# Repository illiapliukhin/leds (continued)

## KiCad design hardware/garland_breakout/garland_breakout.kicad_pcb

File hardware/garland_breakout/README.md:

# Garland breakout v1

A passive fan-out between the mono electronics board's FFC pair and long wire runs (LED nets/garlands, remote panels). It follows [LED_INTERFACE_STANDARD.md](../common/LED_INTERFACE_STANDARD.md). To the cable it looks exactly like a panel: same FH12 footprint, cloned from `mono_panel_32x32` `J_ROW`, on B.Cu, cable exits west, pin 1 north, standard **Type B pin 1→1** FFC.

| | |
|---|---|
| Size | 60 × 145 mm, 2 layers, 1.6 mm, 1 oz, 4 × M3 plated (GND) |
| Inputs | `J_ROW`, `J_COL`: FH12-40S-0.5SH, both on the west edge (row cable above the column cable, so the two cables from `J_ROW1`/`J_COL1` run straight) |
| Outputs | `J_R1` rows 1–16, `J_R2` rows 17–32, `J_C1` cols 1–16, `J_C2` cols 17–32: 2×8 2.54 mm IDC box headers; **header pin n = line n = ribbon conductor n** |
| ESD | 64 × PESD5V0S1BL (bidirectional 5 V, SOD-882) from every line to GND, placed at the bus vias next to the headers |
| Row lines | 0.4 mm on the bus/F.Cu, 0.3 mm between header pins, 0.2 mm only in the 0.5 mm-pitch FFC escape (< 30 mm). Total breakout row resistance < 30 mΩ. |
| ID | `U_ID` 24LC02BT-I/OT at 0x50 on J_ROW 35/36/37, 100 nF, WP = GND; J_ROW 33/38/39/40 = GND (`ID_PRESENT_N` asserted) |
| Sense | `TP_VSENSE`: J_ROW pin 34 brought to a test pad (panel-end VLED/row tap for diagnostics) |
| Injection | `J_INJ` 3.5 mm 2-pole terminal, DNP: pin 1 GND (installation earth / ESD return), pin 2 `VINJ` (reserved for a future active row-repeater. A passive matrix cannot use remote VLED, see the standard §5) |
| J_COL spares | 33/38/40 GND; 34–37, 39 (`EXP_*`) left unconnected (reserved for column expansion) |

Assembly: all SMD on **B.Cu** (one reflow side). Only the IDC headers (and DNP J_INJ) are THT, on F.

Optional row-current sense was considered and left out of v1. Only one row is on at a time, so one shunt in the common `LED_4V1` feed on the main board measures the same thing more accurately than 32 series parts at 1.27 mm pitch. `TP_VSENSE` plus the EEPROM `row_path_mohm` field cover drop diagnostics.

## Files

| File | |
|---|---|
| `gen_garland_breakout.py` | parametric generator (KiCad 10 pcbnew, AppImage python3.11) |
| `make_fab.sh` | regenerate → DRC → renders → gerbers/drill/CPL → `fab/garland_breakout_fab.zip` |
| `garland_breakout.kicad_pcb` / `.kicad_pro` | board |
| `fab/drc_report.txt` | **0 violations, 0 unconnected** (KiCad 10, zones refilled) |
| `fab/garland_breakout_fab.zip` | Gerbers (Cu/mask/paste/silk/edge), Excellon, BOM, CPL |
| `fab/garland_breakout_bom.csv`, `fab/garland_breakout_cpl.csv` | |
| `img/garland_breakout_{top,bottom,iso}.png` | renders (no 3D models in the AppImage, so parts show as pads) |

## Price estimate (JLCPCB/LCSC class, Oct 2026, unverified, ±30 %)

| Item | 5 pcs | 50 pcs |
|---|---:|---:|
| PCB 60×145 2L HASL | ~$10 | ~$35 |
| SMT setup + stencil (one side) | ~$10 | ~$10 |
| Extended-part fees (FH12, PESD, 24LC02) | ~$9 | ~$9 |
| Parts per board: 2× FH12 ($1.8), 64× PESD5V0S1BL ($1.6), 4× IDC 2×8 box ($0.8), 24LC02 + C ($0.25) | ~$22 | ~$200 (~$4.0 ea) |
| Hand-solder 4 IDC headers (THT) | own time | ~$15 |
| **Total** | **≈ $50 (≈ $10/board)** | **≈ $270 (≈ $5.5/board)** |
| + 2 × Type B 40p 0.5 mm FFC 100–150 mm | ~$1/board | |
| + 4 × 16-way IDC sockets + 28 AWG ribbon 3 m | ~$3/board | |

## Bring-up checks

1. Continuity: J_ROW pin n ↔ J_R1/J_R2 pin n, J_COL pin n ↔ J_C1/J_C2 pin n (all 64). TVS to GND reads as a diode both ways (≈ 0.6–7 V on the diode tester; no shorts).
2. Without the main-board ID wiring (see LED_SCALING_OPTIONS.md, main-board changes), firmware falls back to the default profile. The LEDs still work.
3. Program `U_ID` with `firmware/panel_id/mkpanelid.py --preset garland32` (an external SOT-23 clip programmer works before the main board has the ID wiring).

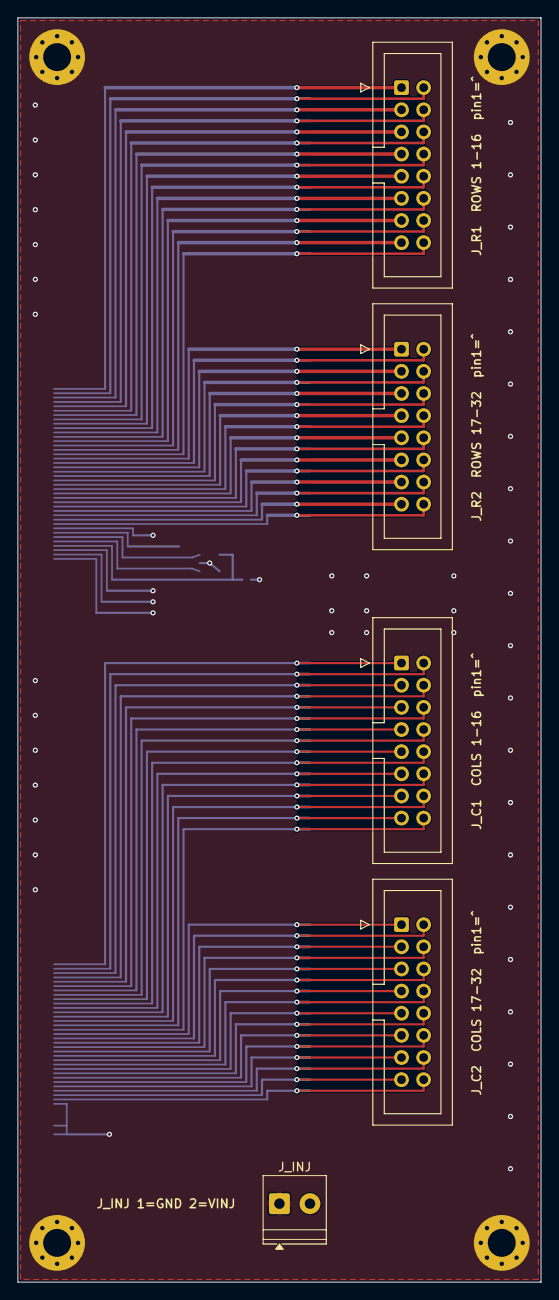
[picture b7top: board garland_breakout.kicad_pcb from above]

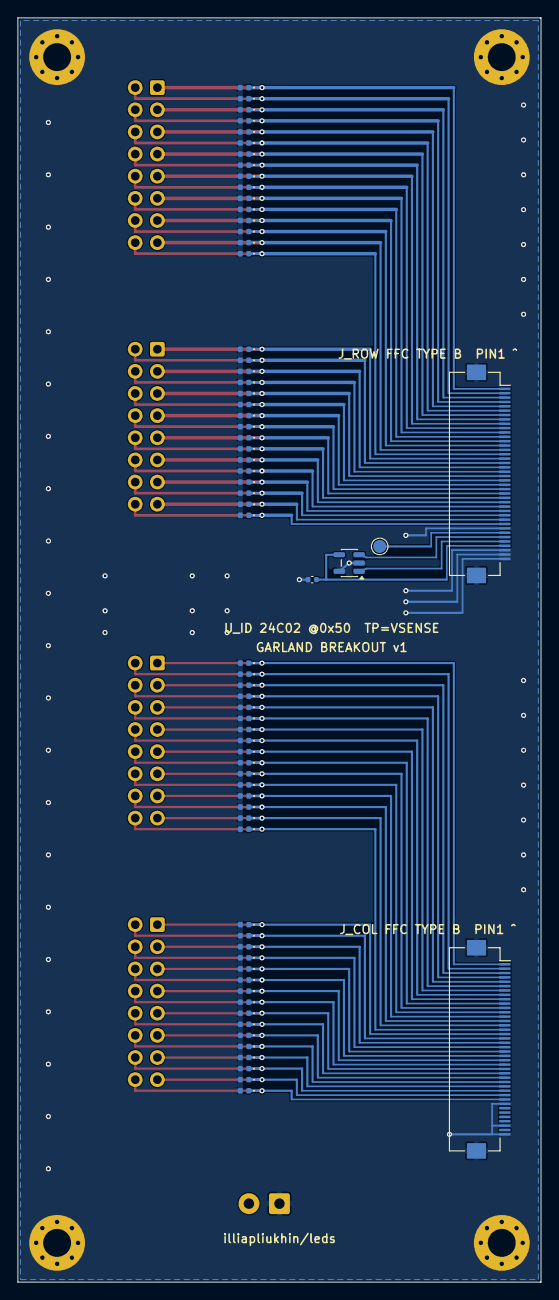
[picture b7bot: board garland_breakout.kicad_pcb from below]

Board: 2 copper layers, 60.0 x 145.0 mm, 78 parts (69 on the bottom side), 69 nets.

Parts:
C_ID: 100n; C_0402_1005Metric
D_C01, D_C02, D_C03, D_C04, D_C05, D_C06, D_C07, D_C08, D_C09, D_C10, D_C11, D_C12, D_C13, D_C14, D_C15, D_C16, D_C17, D_C18, D_C19, D_C20, D_C21, D_C22, D_C23, D_C24, D_C25, D_C26, D_C27, D_C28, D_C29, D_C30, D_C31, D_C32: PESD5V0S1BL; D_0402_1005Metric
D_R01, D_R02, D_R03, D_R04, D_R05, D_R06, D_R07, D_R08, D_R09, D_R10, D_R11, D_R12, D_R13, D_R14, D_R15, D_R16, D_R17, D_R18, D_R19, D_R20, D_R21, D_R22, D_R23, D_R24, D_R25, D_R26, D_R27, D_R28, D_R29, D_R30, D_R31, D_R32: PESD5V0S1BL; D_0402_1005Metric
H1, H2, H3, H4: M3 GND; MountingHole_3.2mm_M3_Pad_Via
J_C1: IDC 2x8 COLS 1-16; IDC-Header_2x08_P2.54mm_Vertical
J_C2: IDC 2x8 COLS 17-32; IDC-Header_2x08_P2.54mm_Vertical
J_COL: FH12-40S-0.5SH; FFC_40P_050_ROW
J_INJ: VINJ/GND (DNP); TerminalBlock_Phoenix_PT-1,5-2-3.5-H_1x02_P3.50mm_Horizontal
J_R1: IDC 2x8 ROWS 1-16; IDC-Header_2x08_P2.54mm_Vertical
J_R2: IDC 2x8 ROWS 17-32; IDC-Header_2x08_P2.54mm_Vertical
J_ROW: FH12-40S-0.5SH; FFC_40P_050_ROW
TP_VSENSE: VLED_SENSE; TestPoint_Pad_D1.5mm
U_ID: 24LC02BT-I/OT; SOT-23-5

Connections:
COL_01: D_C01.1, J_C1.1, J_COL.1
COL_02: D_C02.1, J_C1.2, J_COL.2
COL_03: D_C03.1, J_C1.3, J_COL.3
COL_04: D_C04.1, J_C1.4, J_COL.4
COL_05: D_C05.1, J_C1.5, J_COL.5
COL_06: D_C06.1, J_C1.6, J_COL.6
COL_07: D_C07.1, J_C1.7, J_COL.7
COL_08: D_C08.1, J_C1.8, J_COL.8
COL_09: D_C09.1, J_C1.9, J_COL.9
COL_10: D_C10.1, J_C1.10, J_COL.10
COL_11: D_C11.1, J_C1.11, J_COL.11
COL_12: D_C12.1, J_C1.12, J_COL.12
COL_13: D_C13.1, J_C1.13, J_COL.13
COL_14: D_C14.1, J_C1.14, J_COL.14
COL_15: D_C15.1, J_C1.15, J_COL.15
COL_16: D_C16.1, J_C1.16, J_COL.16
COL_17: D_C17.1, J_C2.1, J_COL.17
COL_18: D_C18.1, J_C2.2, J_COL.18
COL_19: D_C19.1, J_C2.3, J_COL.19
COL_20: D_C20.1, J_C2.4, J_COL.20
COL_21: D_C21.1, J_C2.5, J_COL.21
COL_22: D_C22.1, J_C2.6, J_COL.22
COL_23: D_C23.1, J_C2.7, J_COL.23
COL_24: D_C24.1, J_C2.8, J_COL.24
COL_25: D_C25.1, J_C2.9, J_COL.25
COL_26: D_C26.1, J_C2.10, J_COL.26
COL_27: D_C27.1, J_C2.11, J_COL.27
COL_28: D_C28.1, J_C2.12, J_COL.28
COL_29: D_C29.1, J_C2.13, J_COL.29
COL_30: D_C30.1, J_C2.14, J_COL.30
COL_31: D_C31.1, J_C2.15, J_COL.31
COL_32: D_C32.1, J_C2.16, J_COL.32
GND: C_ID.2, D_C01.2, D_C02.2, D_C03.2, D_C04.2, D_C05.2, D_C06.2, D_C07.2, D_C08.2, D_C09.2, D_C10.2, D_C11.2, D_C12.2, D_C13.2, D_C14.2, D_C15.2, D_C16.2, D_C17.2, D_C18.2, D_C19.2, D_C20.2, D_C21.2, D_C22.2, D_C23.2, D_C24.2, D_C25.2, D_C26.2, D_C27.2, D_C28.2, D_C29.2, D_C30.2, D_C31.2, D_C32.2, D_R01.2, D_R02.2, D_R03.2, D_R04.2, D_R05.2, D_R06.2, D_R07.2, D_R08.2, D_R09.2, D_R10.2, D_R11.2, D_R12.2, D_R13.2, D_R14.2, D_R15.2, D_R16.2, D_R17.2, D_R18.2, D_R19.2, D_R20.2, D_R21.2, D_R22.2, D_R23.2, D_R24.2, D_R25.2, D_R26.2, D_R27.2, D_R28.2, D_R29.2, D_R30.2, D_R31.2, D_R32.2, H1.1, H2.1, H3.1, H4.1, J_COL.33, J_COL.38, J_COL.40, J_COL.MP, J_INJ.1, J_ROW.33, J_ROW.38, J_ROW.39, J_ROW.40, J_ROW.MP, U_ID.2, U_ID.5
ID_3V3: C_ID.1, J_ROW.37, U_ID.4
ID_SCL: J_ROW.36, U_ID.1
ID_SDA: J_ROW.35, U_ID.3
ROW_01: D_R01.1, J_R1.1, J_ROW.1
ROW_02: D_R02.1, J_R1.2, J_ROW.2
ROW_03: D_R03.1, J_R1.3, J_ROW.3
ROW_04: D_R04.1, J_R1.4, J_ROW.4
ROW_05: D_R05.1, J_R1.5, J_ROW.5
ROW_06: D_R06.1, J_R1.6, J_ROW.6
ROW_07: D_R07.1, J_R1.7, J_ROW.7
ROW_08: D_R08.1, J_R1.8, J_ROW.8
ROW_09: D_R09.1, J_R1.9, J_ROW.9
ROW_10: D_R10.1, J_R1.10, J_ROW.10
ROW_11: D_R11.1, J_R1.11, J_ROW.11
ROW_12: D_R12.1, J_R1.12, J_ROW.12
ROW_13: D_R13.1, J_R1.13, J_ROW.13
ROW_14: D_R14.1, J_R1.14, J_ROW.14
ROW_15: D_R15.1, J_R1.15, J_ROW.15
ROW_16: D_R16.1, J_R1.16, J_ROW.16
ROW_17: D_R17.1, J_R2.1, J_ROW.17
ROW_18: D_R18.1, J_R2.2, J_ROW.18
ROW_19: D_R19.1, J_R2.3, J_ROW.19
ROW_20: D_R20.1, J_R2.4, J_ROW.20
ROW_21: D_R21.1, J_R2.5, J_ROW.21
ROW_22: D_R22.1, J_R2.6, J_ROW.22
ROW_23: D_R23.1, J_R2.7, J_ROW.23
ROW_24: D_R24.1, J_R2.8, J_ROW.24
ROW_25: D_R25.1, J_R2.9, J_ROW.25
ROW_26: D_R26.1, J_R2.10, J_ROW.26
ROW_27: D_R27.1, J_R2.11, J_ROW.27
ROW_28: D_R28.1, J_R2.12, J_ROW.28
ROW_29: D_R29.1, J_R2.13, J_ROW.29
ROW_30: D_R30.1, J_R2.14, J_ROW.30
ROW_31: D_R31.1, J_R2.15, J_ROW.31
ROW_32: D_R32.1, J_R2.16, J_ROW.32
VLED_SENSE: J_ROW.34, TP_VSENSE.1

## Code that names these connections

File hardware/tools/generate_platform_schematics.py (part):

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            "FootprintStatus": "RELEASED_MURATA_DFE201612E",
        },
    )
    add_pin_label(schematic, key, "L1", "1", "LED_SW1")
    add_pin_label(schematic, key, "L1", "2", "LED_SW2")
    add_resistor(
        schematic, key, "R3", "655k 0.1%", (185.42, 48.26), "LED_4V1", "LED_FB"
    )
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            "FootprintStatus": "RELEASED_LUCKI_SMD3225_4P",
        },
    )
    add_pin_label(schematic, key, "Y1", "1", "XTAL_P")
    add_pin_label(schematic, key, "Y1", "2", "GND")
    add_pin_label(schematic, key, "Y1", "3", "XTAL_N")
    add_pin_label(schematic, key, "Y1", "4", "GND")
    add_component(
        schematic,
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            "FootprintStatus": "RELEASED_STANDARD_0402",
        },
    )
    add_pin_label(schematic, key, "TH1", "1", "PCB_NTC_ADC")
    add_pin_label(schematic, key, "TH1", "2", "GND")
    add_resistor(
        schematic,
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            "FootprintStatus": "RELEASED_PANASONIC_EVPBL",
        },
    )
    add_pin_label(schematic, key, "SW1", "1", "BUTTON_WAKE_N")
    add_pin_label(schematic, key, "SW1", "2", "GND")
    add_resistor(
        schematic,
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            "FootprintStatus": "RELEASED_GETTOP_V8",
        },
    )
    add_pin_label(schematic, key, "MIC1", "1", "MIC_VDD")
    add_pin_label(schematic, key, "MIC1", "2", "GND")
    add_pin_label(schematic, key, "MIC1", "3", "GND")
    add_pin_label(schematic, key, "MIC1", "4", "MIC_RAW")
    add_component(
        schematic,
        generation_key=key,
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
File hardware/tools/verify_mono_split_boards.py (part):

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    r"\b(?:GND|VBUS|AON_3V3|SYS|REXT1|REXT2|LED_LOGIC_3V3|LED_OE_N|"
    r"LED_CLK(?:_(?:Y|PRE))?|LED_SDI(?:_(?:Y|PRE))?|LED_LE(?:_(?:Y|PRE))?|"
    r"LED_OE_Y|LED_SDO|LED_FB|SW_L1|SW_L2|LED_EN|LED_LOGIC_EN|LED_QOD|"
    r"AUDIO_EN|BAT_RAW|ILIM_VSET|TS_MR|ISET|CHIP_PU|GPIO0_BOOT|"
    r"USB_D_P(?:_MCU)?|USB_D_N(?:_MCU)?|XTAL_P|XTAL_N)\b"
)

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
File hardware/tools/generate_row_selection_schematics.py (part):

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        },
    )

    add_pin_label(schematic, generation_key, reference, "1", "AON_3V3")
    add_pin_label(schematic, generation_key, reference, "2", "AON_3V3")
    for address_index in range(4):
        add_pin_label(
            schematic,
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            str(3 + address_index),
            f"ROW_A{address_index}",
        )
    add_pin_label(schematic, generation_key, reference, "7", "DEC_A_EN_N")
    add_pin_label(schematic, generation_key, reference, "8", "DEC_B_EN_N")
    add_pin_label(
        schematic,
        generation_key,
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
    add_no_connect(schematic, generation_key, reference, "14")
    add_no_connect(schematic, generation_key, reference, "15")
    add_pin_label(schematic, generation_key, reference, "16", "DEC_B_EN_4V1_N")
    add_pin_label(schematic, generation_key, reference, "17", "DEC_A_EN_4V1_N")
    for address_index, pin_number in enumerate(("21", "20", "19", "18")):
        add_pin_label(
            schematic,
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            pin_number,
            f"ROW_A{address_index}_4V1",
        )
    add_pin_label(schematic, generation_key, reference, "22", "ROW_XLAT_OE_N")
    add_pin_label(schematic, generation_key, reference, "23", "LED_4V1")
    add_pin_label(schematic, generation_key, reference, "24", "LED_4V1")

    add_resistor(
        schematic,
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            pin_number,
            f"ROW_A{address_index}_4V1",
        )
    add_pin_label(schematic, generation_key, reference, "24", "LED_4V1")


def get_row_component_position(row_number: int) -> tuple[float, float]:
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        properties={"Function": f"Q_ROW{row_number:02d}"},
    )
    add_pin_label(schematic, generation_key, pmos_reference, "1", gate_net)
    add_pin_label(schematic, generation_key, pmos_reference, "2", "LED_4V1")
    add_pin_label(schematic, generation_key, pmos_reference, "3", row_net)


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
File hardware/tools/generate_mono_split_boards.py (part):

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            0.0,
            14.5,
            10.5,
            {"1": "GPIO0_BOOT", "2": "GND"},
        ),
        PlacedPart(
            "U_ROW_XLAT",
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            0.0,
            40.0,
            17.5,
            {"1": "AON_3V3", "2": "GPIO0_BOOT"},
        ),
        PlacedPart(
            "R_USB_P",
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

def row_select_fan_layer(row_number: int) -> int:
    # ROW_01..11 on In2 (continuous In1 AON pocket); ROW_12 pin13 on In1.
    if 1 <= row_number <= 11:
        return pcbnew.In2_Cu
    return pcbnew.In1_Cu
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        [(aon_spine_x, 10.15), (49.49, 10.15)],
        0.20,
    )
    # Join the east MCU spine into the translator AON bus on In2 (In1 crosses ROW_01_Y @ y≈9.7).
    route_net_polyline(
        board,
        "AON_3V3",
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        ("DEC_A_EN_N", "18", "17", 7.80, 73.35, 61.40, 102.80),
        ("DEC_B_EN_N", "18", "16", 8.25, 74.00, 119.40, 103.30),
    )
    # MCU-side spines stay left of the ROW_A0 drop at x=66.30. The upper pin
    # escapes furthest left so its vertical does not cross the stubs below it.
    mcu_spines = {
        "ROW_A0": (63.80, 18.70),
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
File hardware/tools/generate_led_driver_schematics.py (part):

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        ("power_out", "LED_LOGIC_3V3"),
        ("power_out", "GND"),
    )
    sink_pins = [("input", "LED_SDO_RETURN")]
    sink_pins.extend(
        ("passive", f"COL_{color_name}_{column_number:02d}")
        for color_name in ("R", "G", "B")
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        )

        add_pin_label(schematic, generation_key, driver.reference, "1", "GND")
        add_pin_label(schematic, generation_key, driver.reference, "3", "LED_CLK")
        add_pin_label(schematic, generation_key, driver.reference, "4", "LED_LE")
        add_pin_label(schematic, generation_key, driver.reference, "21", "LED_OE_N")
        add_pin_label(
            schematic,
            generation_key,
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        footprint=CAPACITOR_FOOTPRINT,
        properties={"Function": "U_LED_BUF_DECOUPLING"},
    )
    add_pin_label(schematic, generation_key, "C100", "1", "LED_LOGIC_3V3")
    add_pin_label(schematic, generation_key, "C100", "2", "GND")


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        footprint=RESISTOR_FOOTPRINT,
        properties={"Function": "LED_SDO_RETURN_PULLDOWN"},
    )
    add_pin_label(schematic, generation_key, "R107", "1", "LED_SDO_RETURN")
    add_pin_label(schematic, generation_key, "R107", "2", "GND")

    add_component(
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        footprint=CAPACITOR_FOOTPRINT,
        properties={"Function": "U_LED_SDO_BUF_DECOUPLING"},
    )
    add_pin_label(schematic, generation_key, "C107", "1", "LED_LOGIC_3V3")
    add_pin_label(schematic, generation_key, "C107", "2", "GND")


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
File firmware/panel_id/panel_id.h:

/* Panel ID EEPROM (LED_INTERFACE_STANDARD v1) - stub, not yet linked into mono_split.
 * Record lives at 0x00 of a 24C02-class EEPROM, I2C 7-bit address 0x50, reached
 * through J_ROW1 pins 35 (ID_SDA) / 36 (ID_SCL) / 37 (ID_3V3). Little-endian. */
#pragma once
#include <stdint.h>
#include <stdbool.h>

#define PANEL_ID_I2C_ADDR   0x50
#define PANEL_ID_MAGIC      0x5044454Cu /* "LEDP" */
#define PANEL_ID_REC_LEN    64

typedef enum { PANEL_FLAT = 0, PANEL_LATTICE = 1, PANEL_FULL_BLEED = 2, PANEL_GARLAND = 3,
               PANEL_BREAKOUT_ONLY = 4, PANEL_COL_EXPANSION = 5 } panel_class_t;
typedef enum { LED_WHITE = 0, LED_RED = 1, LED_GREEN = 2, LED_BLUE = 3, LED_AMBER = 4,
               LED_WARM_WHITE = 5 } led_type_t;
/* mapping: logical (x right, y down) -> physical (row, col) on the FFC lines */
typedef enum { MAP_IDENTITY = 0, MAP_MIRROR_X = 1, MAP_MIRROR_Y = 2, MAP_ROT180 = 3,
               MAP_TRANSPOSE = 4, MAP_SERPENTINE_COLS = 5, MAP_TABLE = 0x80 } panel_map_t;

#define PANEL_FLAG_VLED_SENSE   (1u << 0) /* pin 34 carries a panel-end VLED sense */
#define PANEL_FLAG_LONG_WIRES   (1u << 1) /* use pre-discharge + blank_ns from record */
#define PANEL_FLAG_PARTIAL      (1u << 2) /* row/col masks valid (freeform nets)    */

typedef struct __attribute__((packed)) {
    uint32_t magic;          /* 0x00 "LEDP" */
    uint8_t  version;        /* 0x04 = 1 */
    uint8_t  rec_len;        /* 0x05 = 64 */
    uint8_t  panel_class;    /* 0x06 panel_class_t */
    uint8_t  led_type;       /* 0x07 led_type_t */
    uint8_t  rows;           /* 0x08 1..32 lines used on J_ROW */
    uint8_t  cols;           /* 0x09 1..32 (64 with column expansion) */
    uint16_t pitch_um;       /* 0x0A 0 = freeform */
    uint16_t i_led_ua;       /* 0x0C max peak current per LED (sets brightness cap) */
    uint16_t i_row_ma;       /* 0x0E max row current the panel/wires accept */
    uint16_t vf_mv;          /* 0x10 typical LED Vf at i_led */
    uint8_t  mapping;        /* 0x12 panel_map_t */
    uint8_t  flags;          /* 0x13 PANEL_FLAG_* */
    uint16_t blank_ns;       /* 0x14 min blanking around a row change */
    uint16_t predischarge_ns;/* 0x16 all-sinks-on slot with no row selected, 0 = off */
    uint16_t row_path_mohm;  /* 0x18 cable + net row resistance estimate */
    uint16_t hw_rev;         /* 0x1A */
    uint32_t serial;         /* 0x1C */
    char     name[16];       /* 0x20 NUL-padded ASCII, e.g. "mono32_flat" */
    uint32_t row_mask;       /* 0x30 populated rows (bit0 = ROW_01), valid with PARTIAL */
    uint32_t col_mask;       /* 0x34 populated cols */
    uint16_t table_id;       /* 0x38 firmware built-in LUT id when mapping == MAP_TABLE */
    uint8_t  scan_div;       /* 0x3A frame-rate divider: 0/1 = 960 Hz (32.55 us/row), 2 = 480 Hz garland mode (65.1 us/row) */
    uint8_t  reserved[3];    /* 0x3B */
    uint16_t crc16;          /* 0x3E CRC-16/CCITT-FALSE over 0x00..0x3D */
} panel_id_t;
_Static_assert(sizeof(panel_id_t) == PANEL_ID_REC_LEN, "panel_id_t size");

/* Board-specific I2C read: fills buf from EEPROM word address `addr`. Return 0 on ACK. */
typedef int (*panel_i2c_read_fn)(uint8_t dev7, uint8_t addr, uint8_t *buf, uint16_t len);

uint16_t panel_id_crc16(const uint8_t *p, uint16_t n);
/* Probe + validate. On any failure fills *out with the default profile and returns false. */
bool panel_id_read(panel_i2c_read_fn rd, panel_id_t *out);
void panel_id_default(panel_id_t *out);       /* mono_panel_32x32 flat, white, 10 mA */
/* Logical pixel -> physical line indices (0-based). Returns false if outside panel. */
bool panel_map(const panel_id_t *id, uint8_t x, uint8_t y, uint8_t *row, uint8_t *col);
